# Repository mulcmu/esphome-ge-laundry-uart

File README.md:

# ESPHome GE Laundry UART

Local Home Assistant control and monitoring for compatible GE appliances through ESPHome and the appliance's GEA serial bus.

> [!WARNING]
> The appliance uses an 8P8C modular connector that looks like Ethernet, but it is **not Ethernet**. Do not connect it to network equipment.

The project began as an effort to integrate a GE washer and dryer with Home Assistant. An ESP32 powered by the appliance communication port reports information such as remaining time and cycle completion through ESPHome. Early work involved researching the GEA2 and GEA3 protocols and the U+ Connect module; later, [GE Appliances](https://github.com/geappliances) and [FirstBuild](https://firstbuild.com/inventions/home-assistant-adapter/) published additional hardware and protocol information. The maintained ESPHome implementation now lives in [mguaylam/esphome-gea](https://github.com/mguaylam/esphome-gea), while this repository provides compatible hardware, reference configurations, manufacturing files, and enclosures.

## Getting started

### I already have a board

Follow the [firmware setup guide](firmware/README.md) to choose a GEA2 or GEA3 configuration, flash the board, connect it to Home Assistant, and check the status LEDs. The [Rev 2 enclosure](case/rev2/README.md) includes ready-to-print files.

### I want to order a board

Start with [PCB Rev 2.2](pcb/rev2.2/README.md), then follow the [step-by-step ordering guide](pcb/ORDERING.md). Rev 2.2 corrects the known Rev 2.0 and Rev 2.1 board-file problems.

**Current status:** Rev 2.2 is the recommended manufacturing candidate; physical testing is still pending. A JLCPCB quote checked on September 19, 2026 was **$78.07 before shipping and tax for five fully assembled boards**, or about **$15.61 per board**. Prices and component availability can change.

Older boards and the complete change history are listed in the [PCB revision index](pcb/README.md). Hardware contributors should also read the [contribution guide](CONTRIBUTING.md).

## Related projects

- [GE Appliances organization](https://github.com/geappliances)
- [FirstBuild Home Assistant adapter](https://firstbuild.com/inventions/home-assistant-adapter/)
- [puddly/casserole](https://github.com/puddly/casserole)
- [GEMakers/green-bean](https://github.com/GEMakers/green-bean)
- [doitaljosh/gea-interface-board](https://github.com/doitaljosh/gea-interface-board)
- [doitaljosh/ge-appliances-re](https://github.com/doitaljosh/ge-appliances-re)
- [doitaljosh/geabus-documentation](https://github.com/doitaljosh/geabus-documentation)
- [simbaja/gehome](https://github.com/simbaja/gehome)
- [GE Appliances Home Assistant adapter](https://github.com/geappliances/home-assistant-adapter)
- [GE Appliances Home Assistant examples](https://github.com/geappliances/home-assistant-examples)
- [GE Appliances Home Assistant bridge](https://github.com/geappliances/home-assistant-bridge)

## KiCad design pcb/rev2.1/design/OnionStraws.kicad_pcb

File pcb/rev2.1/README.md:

# PCB Rev 2.1

Rev 2.1 is the latest built Rev 2.x design before the corrective Rev 2.2 work. Its KiCad project was migrated to KiCad 9.

> [!WARNING]
> The RX and TX silkscreen labels are swapped. U1 can cause ESP32 boot loops. The manufacturing files are preserved for history and should not be mistaken for a corrected release.

## Files

- [Open the KiCad project](design/OnionStraws.kicad_pro)
- [Schematic source](design/OnionStraws.kicad_sch)
- [PCB source](design/OnionStraws.kicad_pcb)
- [Gerber archive](manufacturing/GERBER-OnionStraws-rev2.1.zip)
- [Bill of materials](manufacturing/BOM-OnionStraws-rev2.1.csv)
- [Component placement list](manufacturing/CPL-OnionStraws-rev2.1.csv)
- [Plated-hole drill map](validation/pth-drill-map.pdf)
- [Non-plated-hole drill map](validation/npth-drill-map.pdf)
- [U1 trace-removal illustration](images/u1-trace-fix.png)

The PCB silkscreen identifies this source as Revision 2.1, while the inherited schematic title block still says 2.0. The historical files are unchanged, and this README calls out the mismatch.

No schematic PDF or board-view image was included with the retained Rev 2.1 artifacts, and those exports were not reconstructed.

[Back to the PCB revision index](../README.md) · [Rev 2 enclosure](../../case/rev2/README.md) · [Firmware examples](../../firmware/README.md)

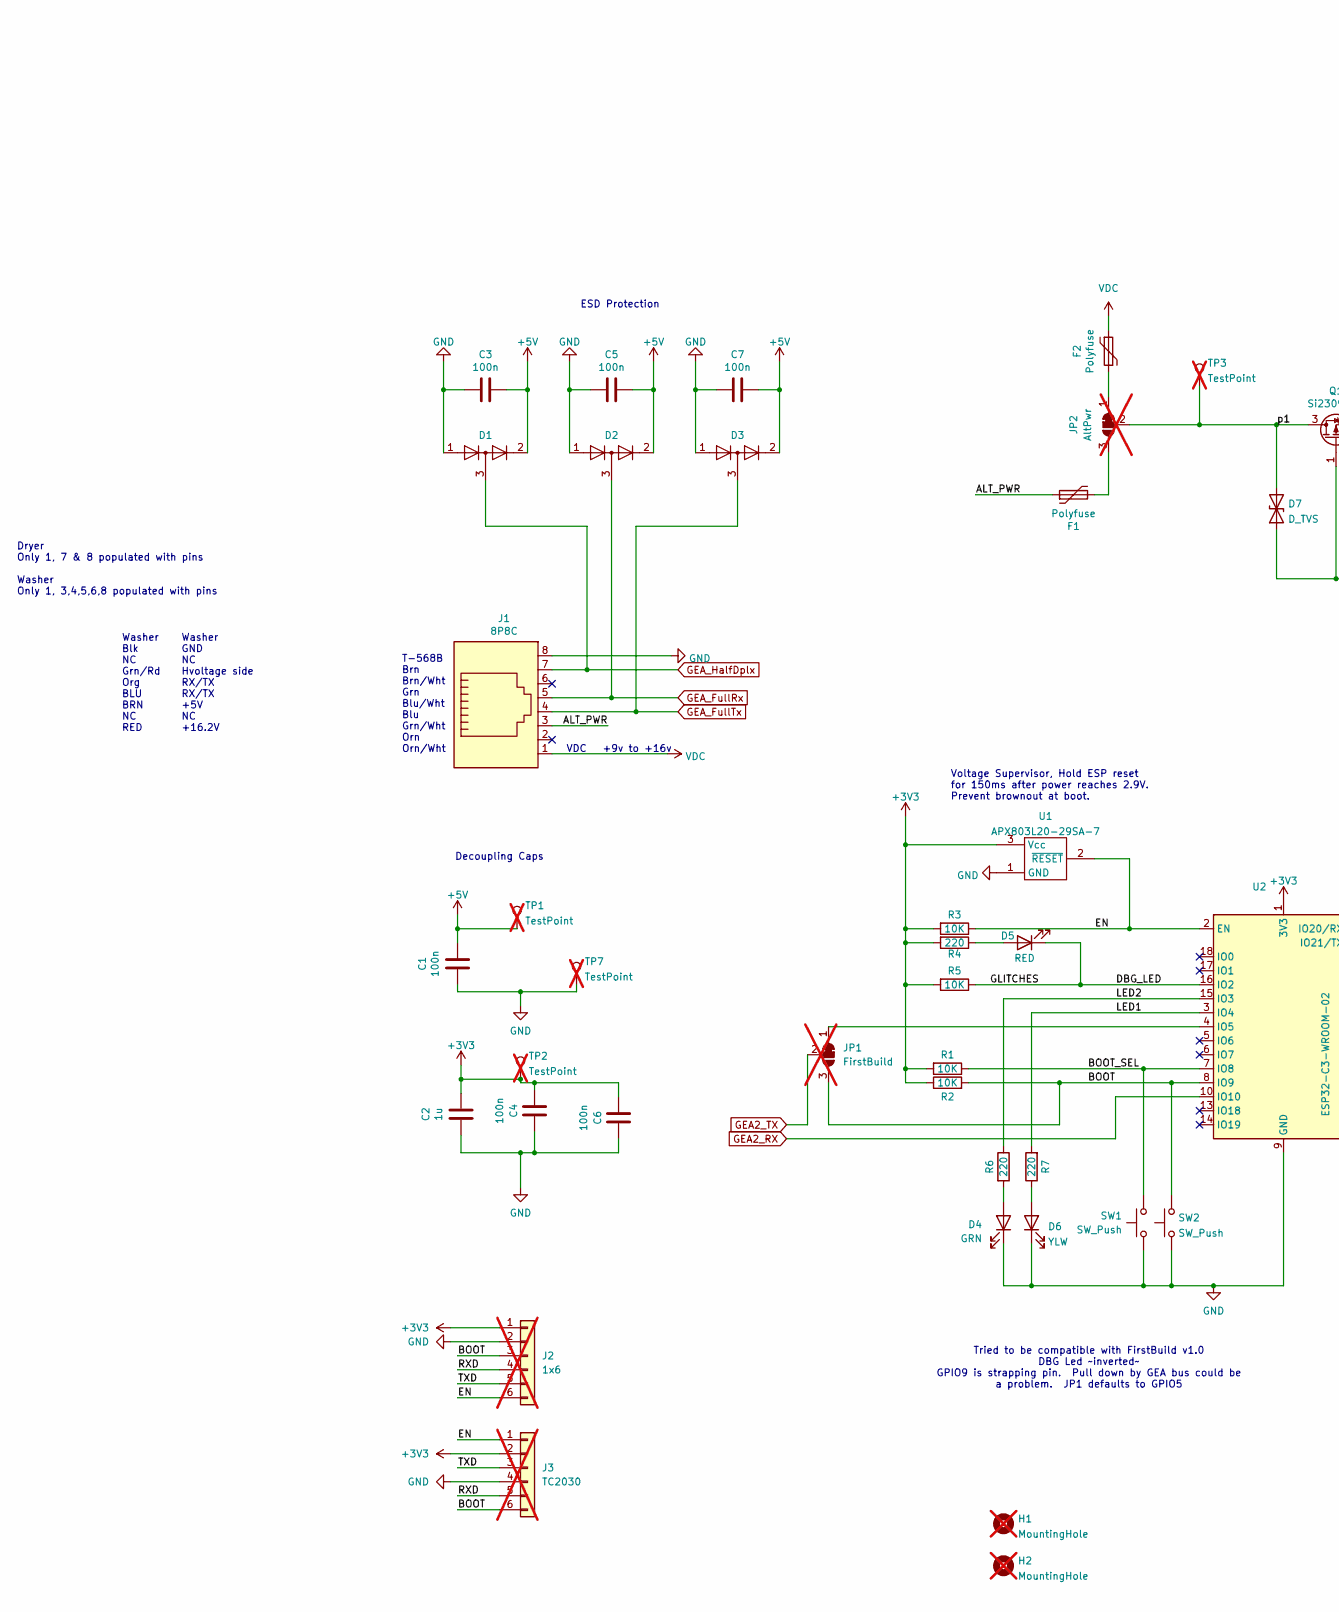
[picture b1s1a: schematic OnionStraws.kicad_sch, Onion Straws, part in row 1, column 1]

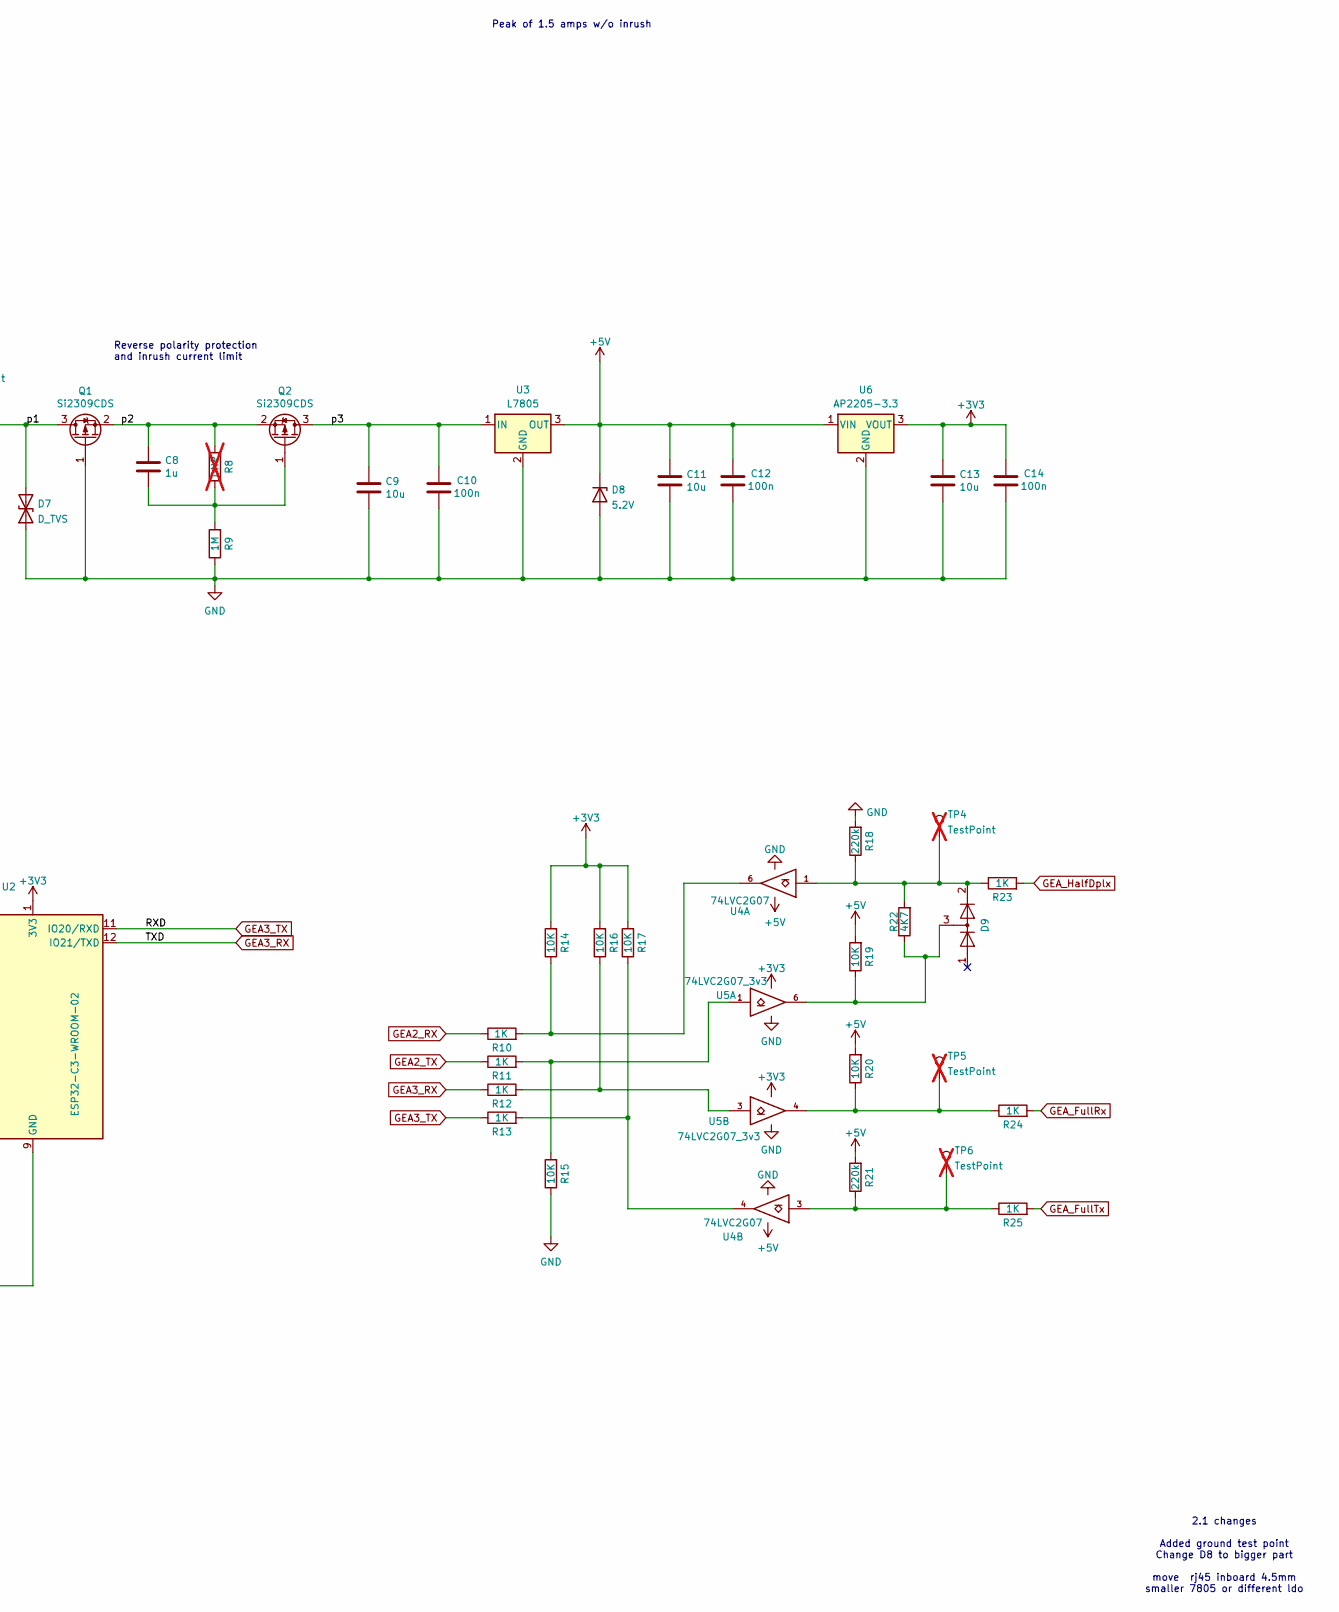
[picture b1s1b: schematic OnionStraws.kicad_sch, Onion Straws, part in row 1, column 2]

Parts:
C1, C3, C4, C5, C6, C7, C10, C12, C14: 100n; C_0805_2012Metric; LCSC C28233
C2, C8: 1u; C_0805_2012Metric; LCSC C28323
C9, C11, C13: 10u; C_0805_2012Metric; LCSC C15850
D1, D2, D3, D9: BAV99; SOT-23; LCSC C2500
D4: GRN; LED_0805_2012Metric; LCSC C2297
D5: RED; LED_0805_2012Metric; LCSC C84256
D6: YLW; LED_0805_2012Metric; LCSC C2296
D7: D_TVS; D_SMA; LCSC C309871
D8: 5.2V; D_SOD-123; LCSC C78479
F1, F2: Polyfuse; Fuse_1812_4532Metric; LCSC C12604
H1, H2: MountingHole; MountingHole_3.2mm_M3_DIN965; not fitted
J1: 8P8C; RJ45_Amphenol_54602-x08_Horizontal; LCSC C3097717
J2: 1x6; PinHeader_1x06_P2.54mm_Vertical; not fitted
J3: TC2030; Tag-Connect_TC2030-IDC-NL_2x03_P1.27mm_Vertical; not fitted
JP1: FirstBuild; SolderJumper-3_P1.3mm_Bridged12_RoundedPad1.0x1.5mm_NumberL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; not fitted
JP2: AltPwr; SolderJumper-3_P1.3mm_Bridged12_RoundedPad1.0x1.5mm_NumberL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; not fitted
Q1: Si2309CDS; SOT-23
Q2: Si2309CDS; SOT-23; LCSC C10493
R1, R2, R3, R5, R14, R15, R16, R17, R19, R20: 10K; R_0805_2012Metric; LCSC C17414
R4, R6, R7: 220; R_0805_2012Metric; LCSC C17557
R8: DNP; R_0805_2012Metric; not fitted
R9: 1M; R_0805_2012Metric; LCSC C17514
R10, R11, R12, R13, R23, R24, R25: 1K; R_0805_2012Metric; LCSC C17513
R18, R21: 220k; R_0805_2012Metric; LCSC C17539
R22: 4K7; R_0805_2012Metric; LCSC C17713
SW1, SW2: SW_Push; SW_Push_1P1T_XKB_TS-1187A; LCSC C318884
TP1, TP2, TP3, TP4, TP5, TP6, TP7: TestPoint; TestPoint_Pad_D2.0mm; not fitted
U1: APX803L20-29SA-7; SOT-23; LCSC C2067355
U2: ESP32-C3-WROOM-02; LCSC C2934560
U3: L7805; TO-263-2; LCSC C86206
U4: 74LVC2G07; SOT-23-6; LCSC C151607
U5: 74LVC2G07_3v3; SOT-23-6; LCSC C151607
U6: AP2205-3.3; SOT-89-3; LCSC C5205181

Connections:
+3V3: C2.1, C4.2, C6.2, C13.1, C14.2, J2.1, J3.2, R1.2, R2.1, R3.2, R4.2, R5.2, R14.2, R16.2, R17.2, TP2.1, U1.3 (Vcc), U2.1 (3V3), U5.5 (+3V3), U6.3 (VOUT)
+5V: C1.1, C3.1, C5.1, C7.1, C11.1, C12.2, D1.2 (A), D2.2 (A), D3.2 (A), D8.1 (K), R19.2, R20.2, R21.2, TP1.1, U3.3 (OUT), U4.5 (VCC), U6.1 (VIN)
/ALT_PWR: F1.1, J1.3
/BOOT: J2.3, J3.6, JP1.3 (B), R2.2, SW2.2, U2.8 (IO9)
/BOOT_SEL: R1.1, SW1.1, U2.7 (IO8)
/DBG_LED: D5.1 (K), R5.1, U2.16 (IO2)
/EN: J2.6, J3.1, R3.1, U1.2 (~RESET), U2.2 (EN)
/LED1: R7.2, U2.3 (IO4)
/LED2: R6.1, U2.15 (IO3)
/p1: D7.2 (A2), JP2.2 (C), Q1.3 (D), TP3.1
/p2: C8.1, Q1.2 (S), Q2.2 (S), R8.2
/p3: C9.1, C10.2, Q2.3 (D), U3.1 (IN)
GEA2_RX: R10.1, U2.10 (IO10)
GEA2_TX: JP1.2 (C), R11.1
GEA3_RX: J2.5, J3.3, R12.1, U2.12 (IO21/TXD)
GEA3_TX: J2.4, J3.5, R13.1, U2.11 (IO20/RXD)
GEA_FullRx: D2.3 (K), J1.5, R24.2
GEA_FullTx: D3.3 (K), J1.4, R25.2
GEA_HalfDplx: D1.3 (K), J1.7, R23.2
GND: C1.2, C2.2, C3.2, C4.1, C5.2, C6.1, C7.2, C9.2, C10.1, C11.2, C12.1, C13.2, C14.1, D1.1 (K), D2.1 (K), D3.1 (K), D4.1 (K), D6.1 (K), D7.1 (A1), D8.2 (A), J1.8, J2.2, J3.4, Q1.1 (G), R9.1, R15.1, R18.2, SW1.2, SW2.1, TP7.1, U1.1 (GND), U2.9 (GND), U2.19 (GND), U3.2 (GND), U4.2 (GND), U5.2 (GND), U6.2 (GND)
unnamed: D4.2 (A), R6.2
unnamed: D5.2 (A), R4.1
unnamed: D6.2 (A), R7.1
unnamed: D9.2 (A), R18.1, R22.2, R23.1, TP4.1, U4.1
unnamed: D9.3 (K), R19.1, R22.1, U5.6
unnamed: JP1.1 (A), U2.4 (IO5)
unnamed: F2.2, JP2.1 (A)
unnamed: F1.2, JP2.3 (B)
unnamed: C8.2, Q2.1 (G), R8.1, R9.2
unnamed: R10.2, R14.1, U4.6
unnamed: R11.2, R15.2, U5.1
unnamed: R12.2, R16.1, U5.3
unnamed: R13.2, R17.1, U4.4
unnamed: R20.1, R24.1, TP5.1, U5.4
unnamed: R21.1, R25.1, TP6.1, U4.3
VDC: F2.1, J1.1

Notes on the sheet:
Voltage Supervisor, Hold ESP reset for 150ms after power reaches 2.9V. Prevent brownout at boot.
Washer Blk NC Grn/Rd Org BLU BRN NC RED
Reverse polarity protection and inrush current limit
Dryer Only 1, 7 & 8 populated with pins Washer Only 1, 3,4,5,6,8 populated with pins
Tried to be compatible with FirstBuild v1.0 DBG Led ~inverted~ GPIO9 is strapping pin. Pull down by GEA bus could be a problem. JP1 defaults to GPIO5
2.1 changes Added ground test point Change D8 to bigger part move rj45 inboard 4.5mm smaller 7805 or different ldo
Washer GND NC Hvoltage side RX/TX RX/TX +5V NC +16.2V
Decoupling Caps
Peak of 1.5 amps w/o inrush
ESD Protection
T-568B Brn Brn/Wht Grn Blu/Wht Blu Grn/Wht Orn Orn/Wht
VDC +9v to +16v

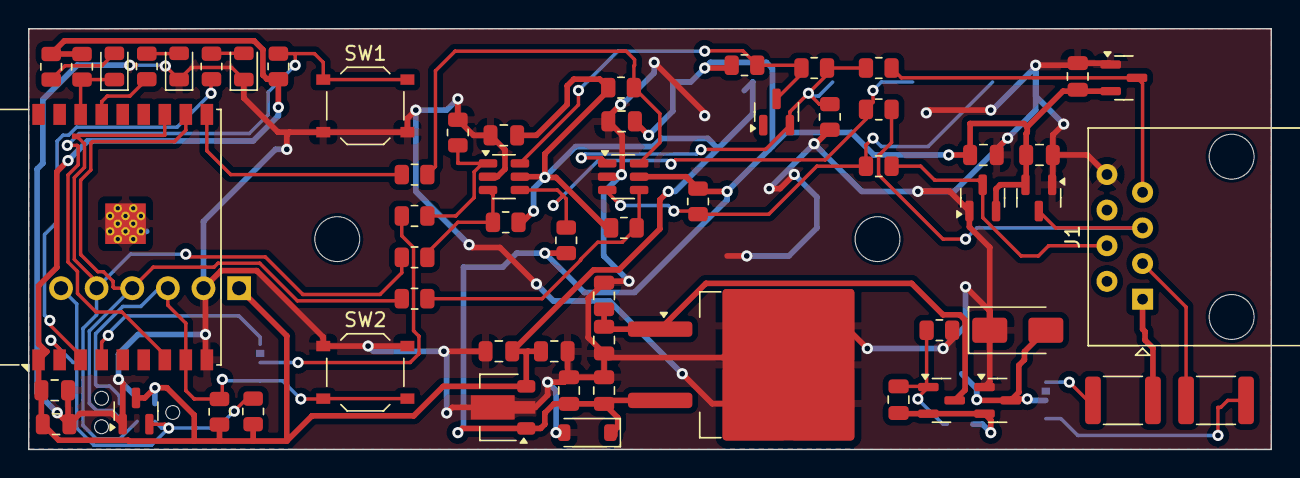
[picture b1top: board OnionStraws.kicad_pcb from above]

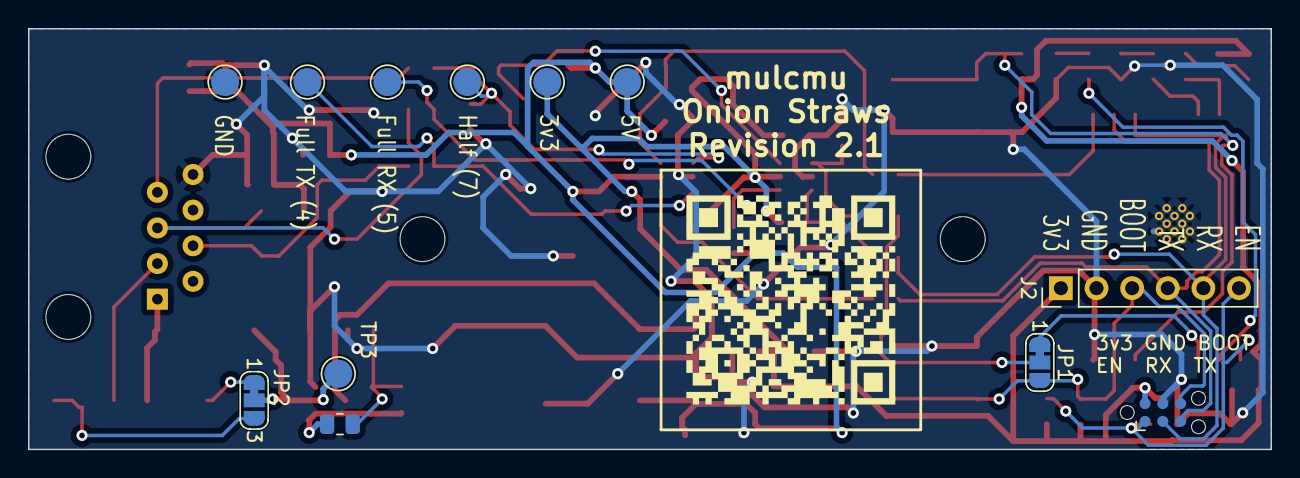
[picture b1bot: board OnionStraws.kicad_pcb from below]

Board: 2 copper layers, 88.6 x 30.0 mm, 74 parts (12 on the bottom side), 36 nets.

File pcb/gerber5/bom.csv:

"Reference","Value","Footprint","Qty","DNP","Description"
"C1,C3,C4,C5,C6,C7,C10,C12,C14","100n","Capacitor_SMD:C_0805_2012Metric","9","","C28233"
"C2,C8","1u","Capacitor_SMD:C_0805_2012Metric","2","","C28323"
"C9,C11,C13","10u","Capacitor_SMD:C_0805_2012Metric","3","","C15850"
"D1,D2,D3,D9","BAV99","Package_TO_SOT_SMD:SOT-23","4","","C2500"
"D4","GRN","LED_SMD:LED_0805_2012Metric","1","","C2297"
"D5","RED","LED_SMD:LED_0805_2012Metric","1","","C84256"
"D6","YLW","LED_SMD:LED_0805_2012Metric","1","","C2296"
"D7","D_TVS","Diode_SMD:D_SMA","1","","C309871"
"D8","5.2V","Diode_SMD:D_SOD-523","1","","C2993047"
"F1,F2","Polyfuse","Fuse:Fuse_1812_4532Metric","2","","C12604"
"H1,H2","MountingHole","MountingHole:MountingHole_3.2mm_M3_DIN965","2","",""
"H3,H4","MountingHole","MountingHole:MountingHole_3.2mm_M3_DIN965","2","DNP",""
"J1","8P8C","Connector_RJ:RJ45_Amphenol_54602-x08_Horizontal","1","","C3097717"
"J2","1x6","Connector_PinHeader_2.54mm:PinHeader_1x06_P2.54mm_Vertical","1","DNP",""
"J3","TC2030","Connector:Tag-Connect_TC2030-IDC-NL_2x03_P1.27mm_Vertical","1","DNP",""
"Q1,Q2","Si2309CDS","Package_TO_SOT_SMD:SOT-23","2","","C10493"
"R1,R2,R3,R5,R14,R15,R16,R17,R19,R20","10K","Resistor_SMD:R_0805_2012Metric","10","","C17414"
"R4,R6,R7","220","Resistor_SMD:R_0805_2012Metric","3","","C17557"
"R8","DNP","Resistor_SMD:R_0805_2012Metric","1","DNP",""
"R9","1M","Resistor_SMD:R_0805_2012Metric","1","","C17514"
"R10,R11,R12,R13,R23,R24,R25","1K","Resistor_SMD:R_0805_2012Metric","7","","C17513"
"R18,R21","220k","Resistor_SMD:R_0805_2012Metric","2","","C17539"
"R22","4K7","Resistor_SMD:R_0805_2012Metric","1","","C17713"
"SW1,SW2","SW_Push","Button_Switch_SMD:SW_Push_1P1T_XKB_TS-1187A","2","","C318884"
"TP1,TP2,TP3,TP4,TP5,TP6","TestPoint","TestPoint:TestPoint_Pad_D2.0mm","6","DNP",""
"U1","APX803L20-29SA-7","Package_TO_SOT_SMD:SOT-23","1","","C2067355"
"U2","ESP32-C3-WROOM-02","RF_Module:ESP32-C3-WROOM-02","1","","C2934560"
"U3","L7805","Package_TO_SOT_SMD:TO-263-2","1","","C86206"
"U4","74LVC2G07","Package_TO_SOT_SMD:SOT-23-6","1","","C151607"
"U5","74LVC2G07_3v3","Package_TO_SOT_SMD:SOT-23-6","1","","C151607"
"U6","AP2205-3.3","Package_TO_SOT_SMD:SOT-89-3","1","","C5205181"

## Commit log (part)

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2021-12-13 ready for testing
2021-12-13 Update README.md
    fix image link
2021-12-15 minor tweaks
2021-12-15 more troubleshooting
2021-12-21 Add wifi status led
2021-12-23 Log packets
2021-12-30 erd for cycle hack
2021-12-30 work on erd info
2021-12-31 more erds from logs
2021-12-31 add remaining time
2022-01-01 add draft pcb files
2022-01-04 basic operation working
2022-01-04 Updated PCB
2022-01-15 dual uart for logging
    2nd uart added for logging both sides of the U+ to Washer communication.
2022-01-15 Update PCB for full duplex
    ESP tx to washer not tested yet
2022-01-16 Updates for Washer
    Basic washer functionality working
2022-01-17 add text for washer sensors
2022-01-17 Update readme & washer erds
2022-01-19 Rev 0.1 of PCB
2022-01-20 Rev 0.2 PCB
    Fix unconnected GND pads
2022-01-29 PCB Rev 0.3
    Fixed D4 and related pull up resistors.
    Added LED and PB
    Added 5V zener diode and TVS for input
2022-01-29 add pcb readme
2022-01-29 Dryer setup for pcb
2022-01-29 separate washer files
2022-01-29 roll back dryer
2022-01-29 update icons
2022-01-29 washer gpio pins
2022-01-29 fix washer return
2022-01-29 add dryer packet ack
2022-02-13 Update readme & erds
    Add door status from @simbaja gehome
2022-02-17 Fix washer use of uninitialized objects
2022-02-19 Add Door State and cycle count
    Cleanup .h to better merge
2022-02-20 Update todo list
2022-02-21 Add BOM
    Add BOM
2022-02-22 Update README.md
    Update README.md
2022-02-24 Dryer yaml has button/led config
2022-03-08 Rework packet reading for escaped bytes
2022-03-25 PCB Rev 1.0
2022-06-22 Add Case
2022-06-23 Add lid with holes
    v7 is plain lid, v8 has holes
2022-06-28 add windows instructions; ignore secrets.yaml explicitly; fix pointer conversion in washer halting compilation; do not assign static ip
2022-07-04 fix readme formatting for display on web page
2022-07-19 Update readme.md
    Fix amazon part identifies
2025-05-11 validation framework for external component
2025-05-13 tx packets
2025-05-15 finish up external component
2025-05-15 add dishwasher
2025-05-15 add dishwasher yaml
2025-05-30 v2 beta
2025-05-30 update v2 case
2025-06-12 pcb 2.1 mods
2025-06-12 fix backslashes in include paths
2025-06-12 add case stls
2025-06-12 case cleanup
2025-07-01 Update gea_adapter.cpp
    add cast for esp-idf call
2026-02-07 Migrate PCB to KiCad 9; add JLC gerbers
2026-05-21 Update repo for current status
    Remove the old local gea_adapter implementation and legacy example YAMLs/docs (washer.yaml, dryer.yaml, dishwasher.yaml, erds.md) along with associated C++/Python component files. Add new GEA2 and GE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
2026-05-21 Fix image link for V2 fix in readme
    Updated image link for V2 fix in readme.
